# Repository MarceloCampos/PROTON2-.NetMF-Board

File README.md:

# PROTON2 .Net MicroFramework Board
 PROTON2 STM32F401 .NetMF Board

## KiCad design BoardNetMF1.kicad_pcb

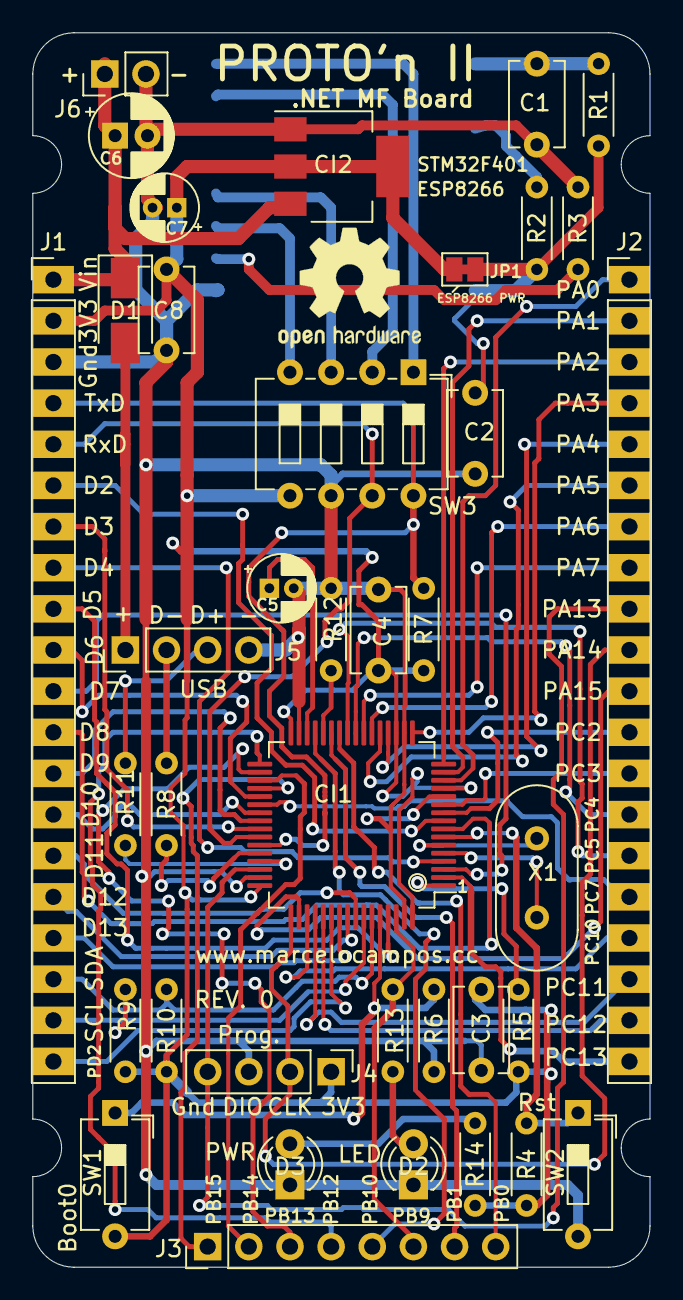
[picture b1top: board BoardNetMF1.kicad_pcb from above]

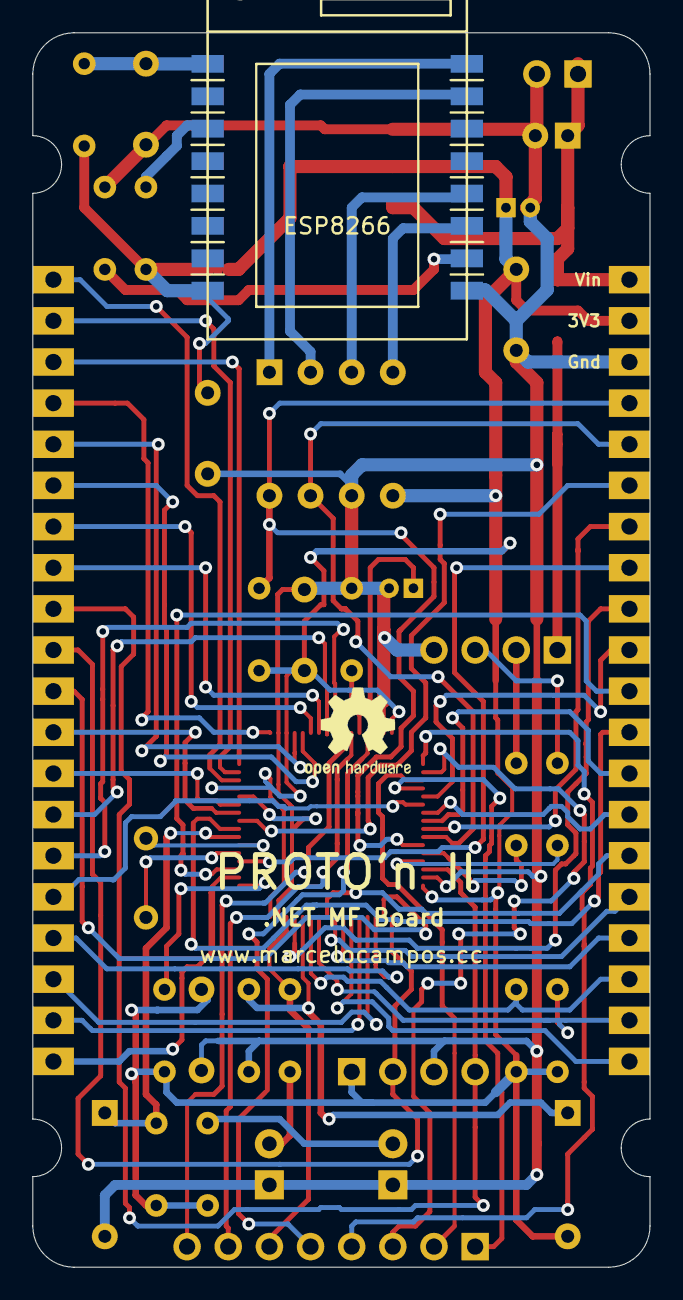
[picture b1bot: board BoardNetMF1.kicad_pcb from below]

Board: 2 copper layers, 38.1 x 76.2 mm, 40 parts (2 on the bottom side), 70 nets.

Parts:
 : OSHW-Logo2_7.3x6mm_SilkScreen
C1, C2, C3, C4, C8: 100 nF; C_Disc_D5.1mm_W3.2mm_P5.00mm
C5: 4.7uF; CP_Radial_D4.0mm_P1.50mm
C6: 100 uF; CP_Radial_D5.0mm_P2.00mm
C7: 10 uF; CP_Radial_D4.0mm_P1.50mm
CI1: STM32F401RETx; LQFP-64_10x10mm_P0.5mm
CI2: LM1117MPX_3.3; SOT-223
D1: 1N4007; D_SMA
D2: VM; LED_D3.0mm
D3: VD; LED_D3.0mm
ESP8266: ESP8266-12; ESP8266
J1, J2: Conn_01x20_Male; PinHeader_1x20_P2.54mm_Vertical_RetangularPads
J3: Conn_01x08_Male; PinHeader_1x08_P2.54mm_Vertical
J4, J5: Conn_01x04_Male; PinHeader_1x04_P2.54mm_Vertical
J6: Conn_01x02_Male; PinHeader_1x02_P2.54mm_Vertical
JP1: Jumper_NC_Small; SolderJumper-2_P1.3mm_Bridged_Pad1.0x1.5mm
R1, R2, R3, R4, R6, R7, R9, R10, R12: 10 K; R_Axial_DIN0204_L3.6mm_D1.6mm_P5.08mm_Horizontal
R5: 33 R; R_Axial_DIN0204_L3.6mm_D1.6mm_P5.08mm_Horizontal
R8, R11: 33r; R_Axial_DIN0204_L3.6mm_D1.6mm_P5.08mm_Horizontal
R13: 680r; R_Axial_DIN0204_L3.6mm_D1.6mm_P5.08mm_Horizontal
R14: 1K; R_Axial_DIN0204_L3.6mm_D1.6mm_P5.08mm_Horizontal
SW1, SW2: SW_Push; SW_DIP_SPSTx01_Slide_6.7x4.1mm_W7.62mm_P2.54mm_LowProfile
SW3: SW_DIP_x04; SW_DIP_SPSTx04_Slide_6.7x11.72mm_W7.62mm_P2.54mm_LowProfile
X1: 8 MHz; Crystal_HC49-4H_Vertical

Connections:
+3V3: C3.1, C4.1, C7.1, C8.1, CI1.13, CI1.19, CI1.32, CI1.48, CI1.64, CI2.2, CI2.4, J1.2, J4.1, JP1.2, R4.1, R5.1, R7.1, R9.2, R10.2, R14.1, SW1.2, SW3.5
/ESP_IO_0: ESP8266.12, SW3.3
/ESP_IO_2: ESP8266.11, SW3.4
/ESP_RXD: ESP8266.15, SW3.2
/ESP_TXD: ESP8266.16, SW3.1
/PA0: CI1.14, J2.1
/PA1: CI1.15, J2.2
/PA2: CI1.16, J2.3
/PA3: CI1.17, J2.4
/PA4: CI1.20, J2.5
/PA5: CI1.21, J2.6
/PA6: CI1.22, J2.7
/PA7: CI1.23, J2.8
/PA8: CI1.41, J1.7
/PA9_TXD: CI1.42, J1.5, SW3.7
/PA10_RXD: CI1.43, J1.4, R7.2, SW3.8
/PA13_SWDIO_PGM: CI1.46, J2.9, J4.4
/PA14_SWCLK_PGM: CI1.49, J2.10, J4.2
/PA15: CI1.50, J2.11
/PB0: CI1.26, J3.8
/PB1: CI1.27, J3.7
/PB3: CI1.55, J1.17
/PB4: CI1.56, J1.16
/PB5: CI1.57, J1.15
/PB6_I2C_SCL: CI1.58, J1.19, R9.1
/PB7_I2C_SDA: CI1.59, J1.18, R10.1
/PB8: CI1.61, J1.9
/PB9_LED: CI1.62, J3.6, R13.1
/PB10: CI1.29, J3.5
/PB12: CI1.33, J3.4
/PB13: CI1.34, J3.3
/PB14: CI1.35, J3.2
/PB15: CI1.36, J3.1
/PC0: CI1.8, J1.12
/PC1: CI1.9, J1.6
/PC2: CI1.10, J2.12
/PC3: CI1.11, J2.13
/PC4: CI1.24, J2.14
/PC5: CI1.25, J2.15
/PC6: CI1.37, J1.10
/PC7: CI1.38, J2.16
/PC8: CI1.39, J1.14
/PC9: CI1.40, J1.13
/PC10: CI1.51, J2.17
/PC11: CI1.52, J2.18
/PC12: CI1.53, J2.19
/PC13: CI1.2, J2.20
/PC14: CI1.3, J1.11
/PC15: CI1.4, J1.8
/PD2: CI1.54, J1.20
/USB.D+: CI1.45, R11.2
/USB.D-: CI1.44, R8.2
GND: C1.2, C2.2, C3.2, C4.2, C5.2, C6.2, C7.2, C8.2, CI1.12, CI1.18, CI1.31, CI1.47, CI1.63, CI2.1, D2.1, D3.1, ESP8266.9, J1.3, J4.3, J5.4, J6.2, R3.2, R6.1, R12.1, SW2.2, SW3.6
unnamed: C1.1, ESP8266.1, R1.2
unnamed: C2.1, ESP8266.8, JP1.1, R1.1, R2.1
unnamed: C5.1, CI1.30
unnamed: CI1.1, R5.2
unnamed: CI1.5, X1.1
unnamed: CI1.6, X1.2
unnamed: CI1.7, R4.2, SW2.1
unnamed: CI1.28, R12.2
unnamed: CI1.60, R6.2, SW1.1
unnamed: D1.2, J5.1
unnamed: D2.2, R13.2
unnamed: D3.2, R14.2
unnamed: J5.2, R8.1
unnamed: J5.3, R11.1
unnamed: ESP8266.3, R2.2
unnamed: ESP8266.10, R3.1
VCC: C6.1, CI2.3, D1.1, J1.1, J6.1

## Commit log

2020-03-26 first commit
    upload
2020-03-26 add image
2020-03-27 adicionado zip com softs arquivos necessários
2020-03-27 add pdf instruc
2020-03-27 add VS
2020-03-29 rev 0.1
2020-07-15 Add files via upload
    Adicionar 'TinyCLR OS Project System v1.0.0.vsix' no VS2017 em Ferramentas-> Extensões e Atualizações
    Nota: desabilitar atualizar automática dessa extensão para que ela não 'quebre' atualizando pra v2.0
2026-01-28 Update LICENSE.md
    + Licensed under CERN-OHL-S v2 or any later version
